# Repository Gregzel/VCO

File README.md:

# VCO-eagle
Realisation d'un Oscillateur Commandé en Tension

Documentation, layout dans le dossier VCO.

## Logiciel

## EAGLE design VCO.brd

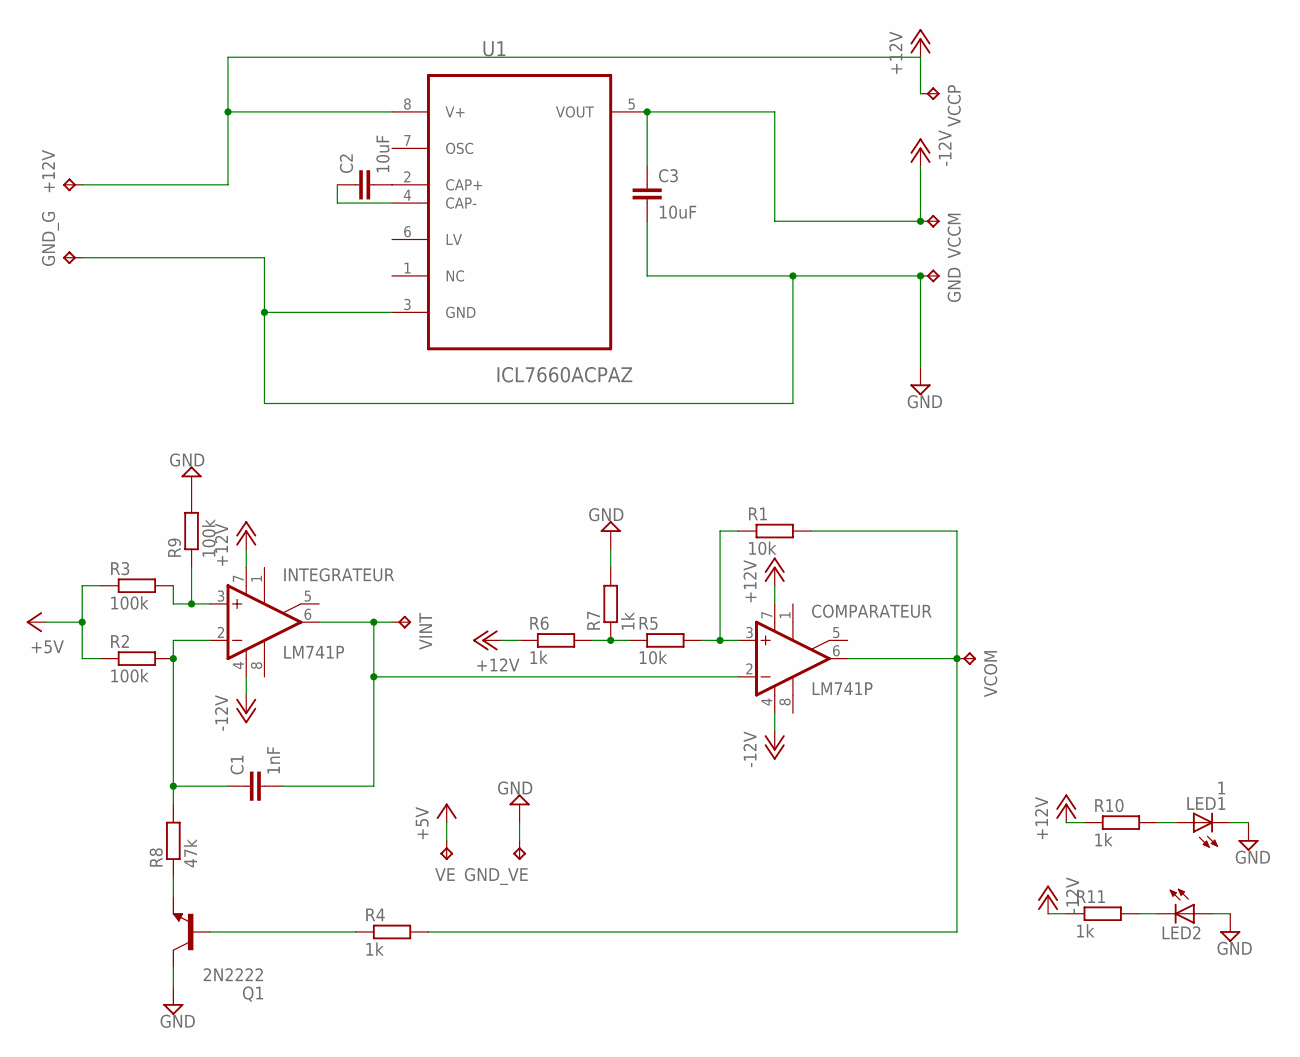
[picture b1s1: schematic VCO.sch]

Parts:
+12V: TPPAD1-13; P1-13
C1: 1nF; C050-025X075
C2, C3: 10uF; C050-025X075
COMPARATEUR: LM741P; DIL08
GND: TPPAD1-13; P1-13
GND_G: TPPAD1-13; P1-13
GND_VE: TPPAD1-13; P1-13
INTEGRATEUR: LM741P; DIL08
LED1: 1; LED5MM
LED2: LED5MM
Q1: 2N2222; TO18
R1, R5: 10k; 0204/7
R2, R3, R9: 100k; 0204/7
R4, R6, R7, R10, R11: 1k; 0204/7
R8: 47k; 0204/7
U1: ICL7660ACPAZ; DIP254P762X533-8
VCCM: TPPAD1-13; P1-13
VCCP: TPPAD1-13; P1-13
VCOM: TPPAD1-13; P1-13
VE: TPPAD1-13; P1-13
VINT: TPPAD1-13; P1-13

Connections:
+5V: R2.1, R3.1, VE.TP
+12V: +12V.TP, COMPARATEUR.7 (V+), INTEGRATEUR.7 (V+), R6.1, R10.1, U1.8 (V+), VCCP.TP; also elsewhere on the board
-12V: C3.1, COMPARATEUR.4 (V-), INTEGRATEUR.4 (V-), R11.1, U1.5 (VOUT), VCCM.TP
GND: C3.2, GND.TP, GND_G.TP, GND_VE.TP, LED1.K (C), LED2.A, Q1.3 (C), R7.2, R9.2, U1.3 (GND)
unnamed: C2.2, U1.2 (CAP+)
unnamed: INTEGRATEUR.3 (+IN), R3.2, R9.1
unnamed: Q1.1 (E), R8.1
unnamed: Q1.2 (B), R4.1
unnamed: C1.1, INTEGRATEUR.2 (-IN), R2.2, R8.2
unnamed: C1.2, COMPARATEUR.2 (-IN), INTEGRATEUR.6 (OUT), VINT.TP
unnamed: R5.1, R6.2, R7.1
unnamed: COMPARATEUR.3 (+IN), R1.1, R5.2
unnamed: COMPARATEUR.6 (OUT), R1.2, R4.2, VCOM.TP
unnamed: LED1.A, R10.2
unnamed: LED2.K (C), R11.2
S$14: C2.1, U1.4 (CAP-)

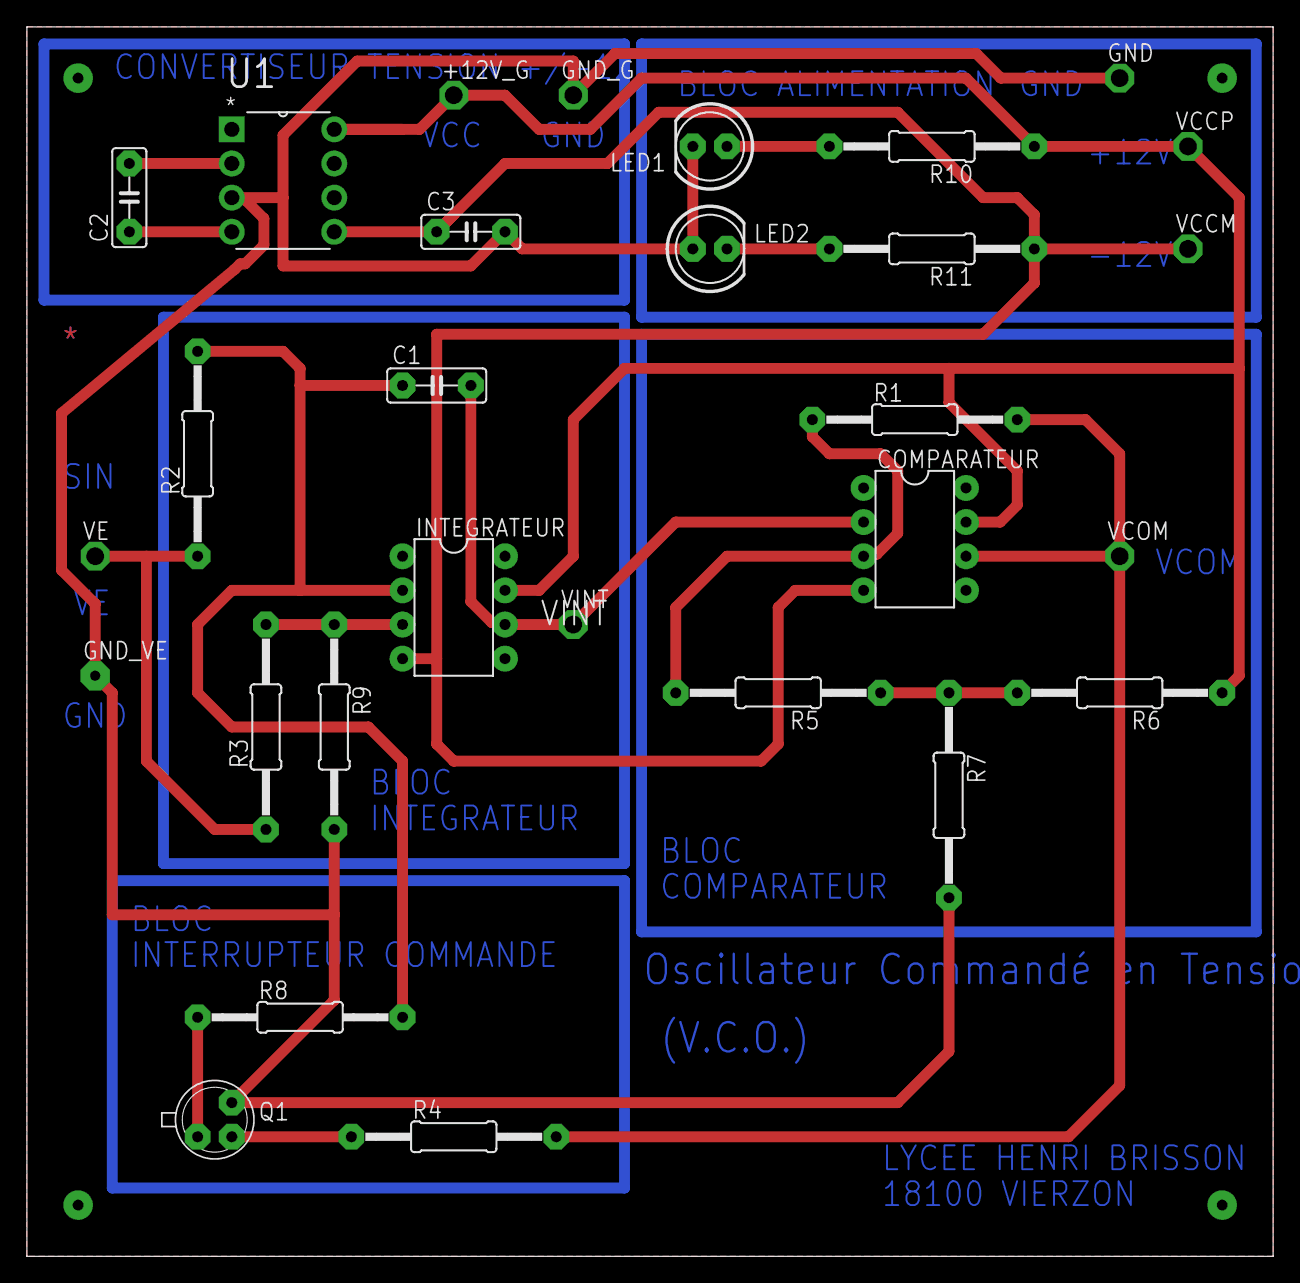
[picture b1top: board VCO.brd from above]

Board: 2 copper layers, 92.7 x 91.4 mm, 29 parts (0 on the bottom side), 16 nets.

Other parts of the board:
+12V_G: TPSPAD1-20; P1-13

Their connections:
+12V: +12V_G.TP; also elsewhere on the board
